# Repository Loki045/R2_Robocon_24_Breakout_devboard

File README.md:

# R2_Robocon_24_Breakout_devboard
ESP32-S3 based breakout PCB designed for Robocon 2024 R2 autonomous robot, supporting sensor interfacing, motor control, and rapid testing of navigation and ball-handling mechanisms.

# Robocon 2024 – R2 Autonomous Breakout PCB with Devboard 

This repository contains the hardware design files for the **R2 Breakout PCB** used for testing Robocon 2024 autonomous robot.

The board was designed as a **ESP32-S3 stackable breakout and testing interface**, enabling direct connection of sensors, motors, and power modules required for autonomous robot development.

---

## 📌 Robot Task Overview

In Robocon 2024, **Robot 2 (R2)** was designed as a fully autonomous robot.

Its primary tasks included:

- Following a predefined path using line follower sensors
- Navigating toward **Area 3**
- Detecting team-colored balls placed in Area 3 (Red/Blue)
- Picking balls and placing them into designated silos

The R2 with devboard breakout PCB enabled rapid testing and integration of sensors, locomotion motors, and mechanism motors required for autonomous navigation and ball placement.

---

## ⚙️ Board Overview

The R2 PCB was developed as a **Initial testing and integration platform**, allowing:

- Direct stacking of **ESP32-S3 Development Board**
- Easy connection of multiple sensors
- Support for locomotion and mechanism motors
- Clean distribution of regulated power inputs
- Rapid hardware testing during autonomous robot development

This modular design simplified debugging and allowed flexible hardware testing during algorithm development.

---

## 🔧 Key Features

- ESP32-S3 compatible stacking layout
- Multiple sensor interface connectors
- Motor control connectors
- Power input connector
- On-board LED indicators
- Decoupling capacitors for stable operation
- Pull-up / current limiting resistors
- Dedicated GPIO breakout headers

---

## 🔌 Supported Sensors

This PCB supported direct connection of commonly used autonomous sensors.

### Sensors Used:

- 6 × Luna Distance Sensors
- MPU9250 (IMU Sensor)
- LSA1 Line Follower Sensor

These sensors were used for navigation, obstacle detection, and path following.

---

## 🎮 Motor Interfaces

The board supported both locomotion and mechanism motors.

### Locomotion Motors:

- 4 Motor connectors for drive system

### Mechanism Motors:

- 2 Motor connectors for grab and lift mechanism

These motors supported locomotion and ball placement operations in silo .

---

## ⚡ Power Interface

Power was supplied through an external regulated source.

### Input:

- Power Input Connector (Voltage supplied externally)

### On-board Components:

- Capacitors for filtering
- Resistors for signal stability
- LED indicators for power/status

---

## 🧠 Application in Autonomous Robot

This breakout board enabled:

- Sensor testing and calibration
- Autonomous navigation testing
- Motor control validation
- Rapid integration of hardware modules

It played a key role in enabling the autonomous behavior of **R2 robot** during Robocon 2024.

---

## 🧰 Hardware Stack

Designed to support:

- ESP32-S3 (Main Controller)
- Line Follower Sensors
- Distance Sensors (Luna)
- MPU9250 (IMU)
- Motor Drivers
- External Power Supply

---

## 📂 Repository Contents

Images/

    ├── R2_3D.png  
    ├── R2_Bottom.png  
    ├── R2_Schematic.png  
    ├── R2_Top.png 

R2_RCU_2024-25

    ├── R2_Breakout.sch  
    ├── R2_Breakout.pcb  
    ├── R2_Breakout.pro      

.gitignore 

README.md

---

## 🛠 Tools Used

- KiCad — Schematic & PCB Design
- ESP-IDF (for ESP32-S3 firmware)

---

## 🎯 Application

This PCB was used in initial testing the **Robocon 2024 R2 Autonomous Robot**, supporting sensor integration, navigation testing, and mechanism control required for ball detection and silo placement.

---

## 👨‍💻 Contribution

Developed as part of Robocon 2024 electronics development, contributing to hardware integration and breakout design for autonomous robot testing.

---

## 📸 PCB Images

### Top Layer

### Bottom Layer

### 3D View

### Schematic

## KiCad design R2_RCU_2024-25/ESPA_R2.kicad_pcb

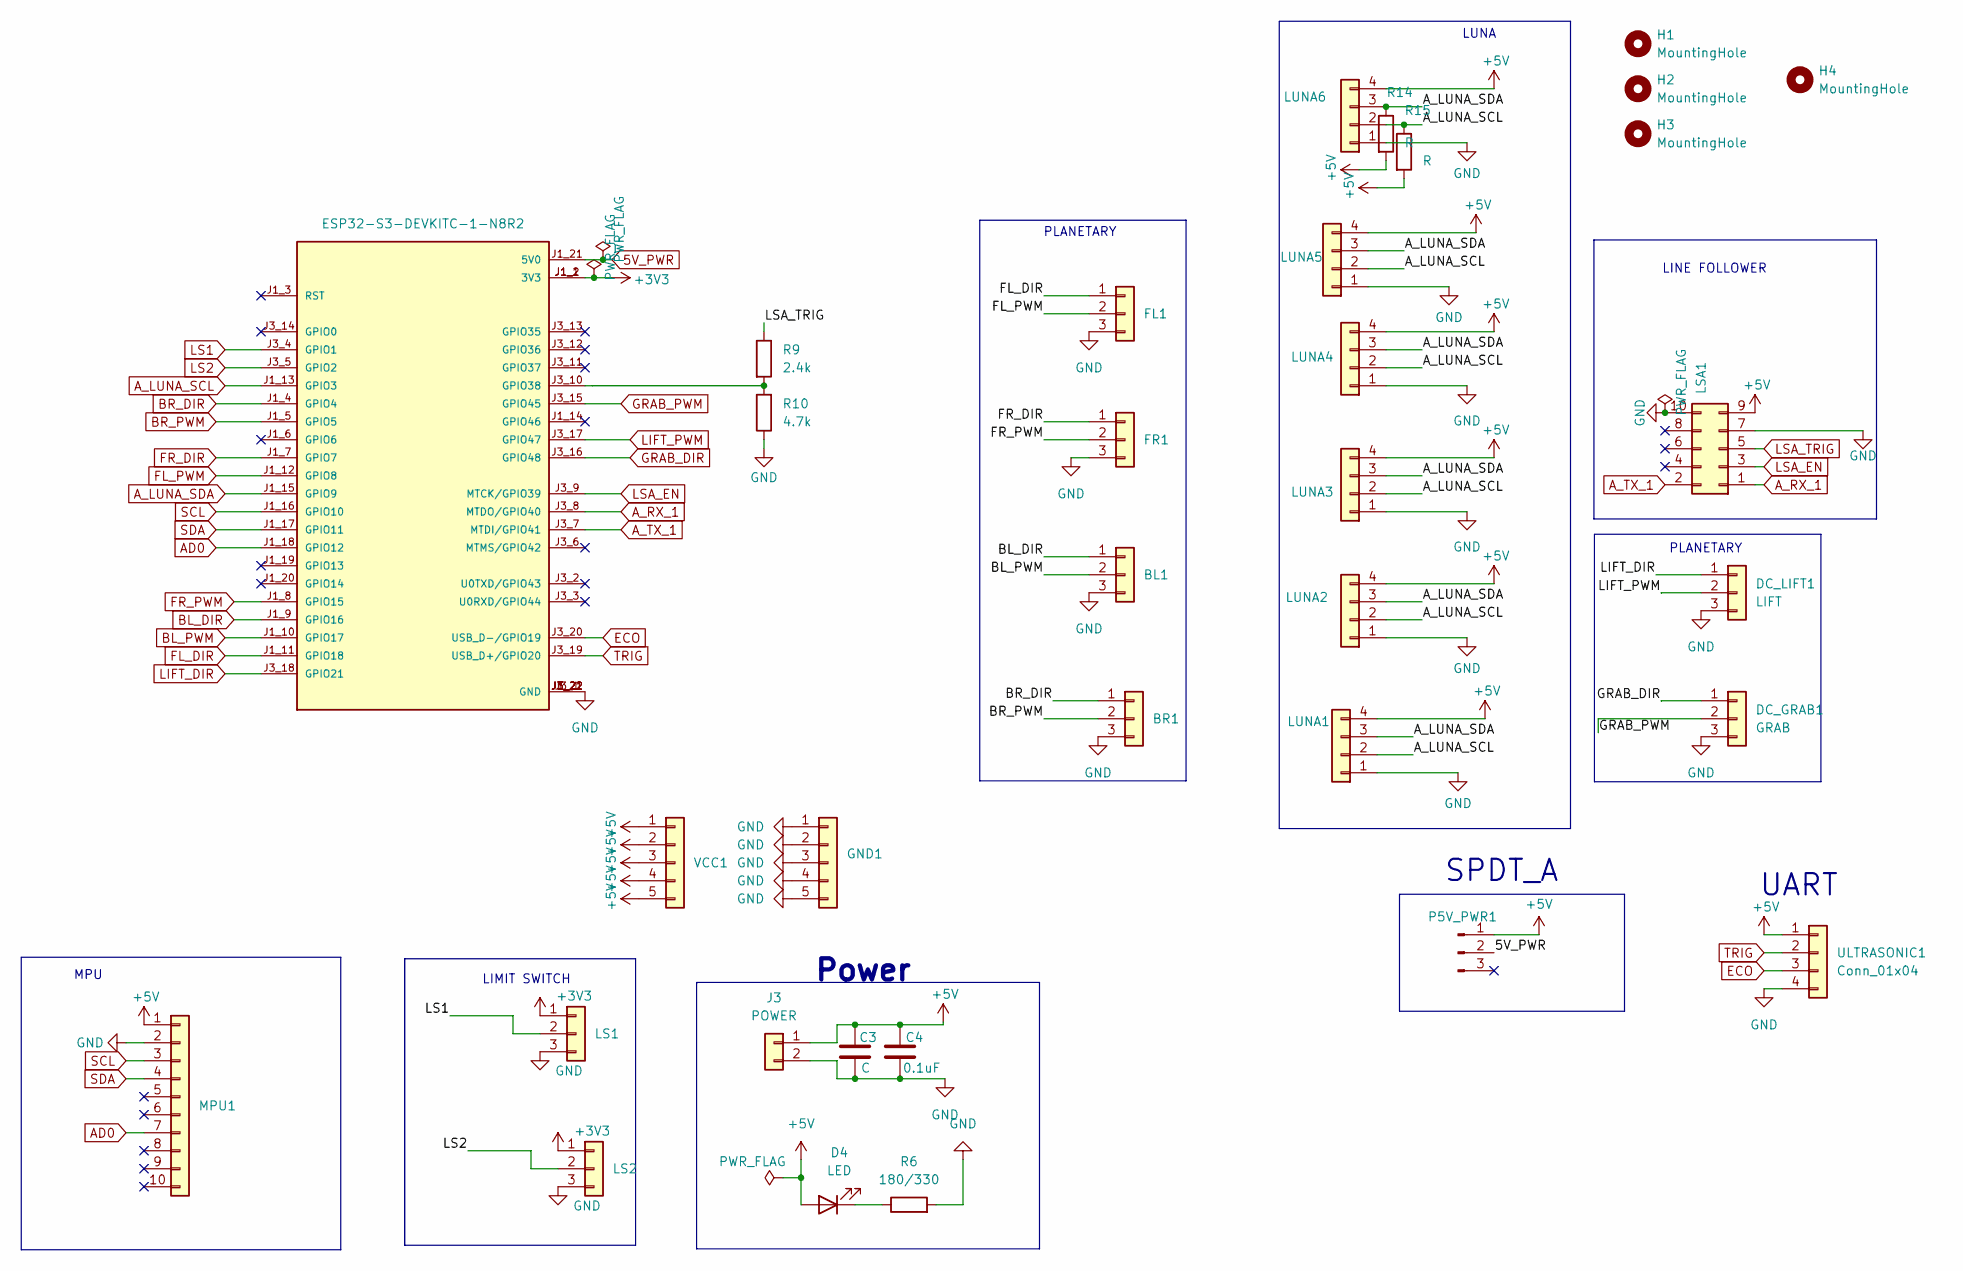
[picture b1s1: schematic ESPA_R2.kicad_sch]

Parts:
BL1: BL; JST_XH_B3B-XH-A_1x03_P2.50mm_Vertical
BR1: BR; JST_XH_B3B-XH-A_1x03_P2.50mm_Vertical
C3: C; C_Radial_D6.3mm_H11.0mm_P2.50mm
C4: 0.1uF; C_Disc_D3.0mm_W1.6mm_P2.50mm
D4: LED; LED_D5.0mm
DC_GRAB1: GRAB; JST_XH_B3B-XH-A_1x03_P2.50mm_Vertical
DC_LIFT1: LIFT; JST_XH_B3B-XH-A_1x03_P2.50mm_Vertical
ESP32-S3-DEVKITC-1-N8R2: ESP32-S3-DEVKITC-1-N8R2; XCVR_ESP32-S3-DEVKITC-1-N8R2; PARTREV V1
FL1: FL; JST_XH_B3B-XH-A_1x03_P2.50mm_Vertical
FR1: FR; JST_XH_B3B-XH-A_1x03_P2.50mm_Vertical
GND1: GND; PinHeader_1x05_P2.54mm_Vertical
H1, H2, H3, H4: MountingHole; MountingHole_2.2mm_M2_ISO14580_Pad
J3: POWER; JST_VH_B2P-VH_1x02_P3.96mm_Vertical
LS1, LS2: FR; JST_XH_B3B-XH-A_1x03_P2.50mm_Vertical
LSA1: Conn_02x05_Counter_Clockwise; IDC-Header_2x05_P2.54mm_Vertical
LUNA1: LUNA1; JST_XH_B4B-XH-A_1x04_P2.50mm_Vertical
LUNA2: LUNA2; JST_XH_B4B-XH-A_1x04_P2.50mm_Vertical
LUNA3: LUNA3; JST_XH_B4B-XH-A_1x04_P2.50mm_Vertical
LUNA4: LUNA4; JST_XH_B4B-XH-A_1x04_P2.50mm_Vertical
LUNA5: LUNA5; JST_XH_B4B-XH-A_1x04_P2.50mm_Vertical
LUNA6: LUNA6; JST_XH_B4B-XH-A_1x04_P2.50mm_Vertical
MPU1: MPU; PinSocket_1x10_P2.54mm_Vertical
P5V_PWR1: 5V_PWR; PinHeader_1x03_P2.54mm_Vertical
R6: 180/330; R_Axial_DIN0204_L3.6mm_D1.6mm_P5.08mm_Horizontal
R9: 2.4k; R_Axial_DIN0204_L3.6mm_D1.6mm_P5.08mm_Horizontal
R10: 4.7k; R_Axial_DIN0204_L3.6mm_D1.6mm_P5.08mm_Horizontal
R14, R15: R; R_Axial_DIN0204_L3.6mm_D1.6mm_P5.08mm_Horizontal
ULTRASONIC1: Conn_01x04; PinHeader_1x04_P2.54mm_Vertical
VCC1: Conn_01x05; PinHeader_1x05_P2.54mm_Vertical

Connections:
5V_PWR: ESP32-S3-DEVKITC-1-N8R2.J1_21 (5V0), P5V_PWR1.2
+3V3: ESP32-S3-DEVKITC-1-N8R2.J1_1 (3V3), ESP32-S3-DEVKITC-1-N8R2.J1_2 (3V3), LS1.1, LS2.1
+5V: C3.1, C4.2, D4.2 (A), J3.1, LSA1.9, LUNA1.4, LUNA2.4, LUNA3.4, LUNA4.4, LUNA5.4, LUNA6.4, MPU1.1, P5V_PWR1.1, R14.2, R15.2, ULTRASONIC1.1, VCC1.1, VCC1.2, VCC1.3, VCC1.4, VCC1.5
AD0: ESP32-S3-DEVKITC-1-N8R2.J1_18 (GPIO12), MPU1.7
A_LUNA_SCL: ESP32-S3-DEVKITC-1-N8R2.J1_13 (GPIO3), LUNA1.2, LUNA2.2, LUNA3.2, LUNA4.2, LUNA5.2, LUNA6.2, R15.1
A_LUNA_SDA: ESP32-S3-DEVKITC-1-N8R2.J1_15 (GPIO9), LUNA1.3, LUNA2.3, LUNA3.3, LUNA4.3, LUNA5.3, LUNA6.3, R14.1
A_RX_1: ESP32-S3-DEVKITC-1-N8R2.J3_8 (MTDO/GPIO40), LSA1.1
A_TX_1: ESP32-S3-DEVKITC-1-N8R2.J3_7 (MTDI/GPIO41), LSA1.2
BL_DIR: BL1.1, ESP32-S3-DEVKITC-1-N8R2.J1_9 (GPIO16)
BL_PWM: BL1.2, ESP32-S3-DEVKITC-1-N8R2.J1_10 (GPIO17)
BR_DIR: BR1.1, ESP32-S3-DEVKITC-1-N8R2.J1_4 (GPIO4)
BR_PWM: BR1.2, ESP32-S3-DEVKITC-1-N8R2.J1_5 (GPIO5)
ECO: ESP32-S3-DEVKITC-1-N8R2.J3_20 (USB_D-/GPIO19), ULTRASONIC1.3
FL_DIR: ESP32-S3-DEVKITC-1-N8R2.J1_11 (GPIO18), FL1.1
FL_PWM: ESP32-S3-DEVKITC-1-N8R2.J1_12 (GPIO8), FL1.2
FR_DIR: ESP32-S3-DEVKITC-1-N8R2.J1_7 (GPIO7), FR1.1
FR_PWM: ESP32-S3-DEVKITC-1-N8R2.J1_8 (GPIO15), FR1.2
GND: BL1.3, BR1.3, C3.2, C4.1, DC_GRAB1.3, DC_LIFT1.3, ESP32-S3-DEVKITC-1-N8R2.J1_22 (GND), ESP32-S3-DEVKITC-1-N8R2.J3_1 (GND), ESP32-S3-DEVKITC-1-N8R2.J3_21 (GND), ESP32-S3-DEVKITC-1-N8R2.J3_22 (GND), FL1.3, FR1.3, GND1.1, GND1.2, GND1.3, GND1.4, GND1.5, J3.2, LS1.3, LS2.3, LSA1.7, LSA1.10, LUNA1.1, LUNA2.1, LUNA3.1, LUNA4.1, LUNA5.1, LUNA6.1, MPU1.2, R6.2, R10.1, ULTRASONIC1.4
GRAB_DIR: DC_GRAB1.1, ESP32-S3-DEVKITC-1-N8R2.J3_16 (GPIO48)
GRAB_PWM: DC_GRAB1.2, ESP32-S3-DEVKITC-1-N8R2.J3_15 (GPIO45)
LIFT_DIR: DC_LIFT1.1, ESP32-S3-DEVKITC-1-N8R2.J3_18 (GPIO21)
LIFT_PWM: DC_LIFT1.2, ESP32-S3-DEVKITC-1-N8R2.J3_17 (GPIO47)
LS1: ESP32-S3-DEVKITC-1-N8R2.J3_4 (GPIO1), LS1.2
LS2: ESP32-S3-DEVKITC-1-N8R2.J3_5 (GPIO2), LS2.2
LSA_EN: ESP32-S3-DEVKITC-1-N8R2.J3_9 (MTCK/GPIO39), LSA1.3
LSA_TRIG: LSA1.5, R9.1
unnamed: D4.1 (K), R6.1
unnamed: ESP32-S3-DEVKITC-1-N8R2.J3_10 (GPIO38), R9.2, R10.2
SCL: ESP32-S3-DEVKITC-1-N8R2.J1_16 (GPIO10), MPU1.3
SDA: ESP32-S3-DEVKITC-1-N8R2.J1_17 (GPIO11), MPU1.4
TRIG: ESP32-S3-DEVKITC-1-N8R2.J3_19 (USB_D+/GPIO20), ULTRASONIC1.2

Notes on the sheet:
UART
LIMIT SWITCH
MPU
PLANETARY
SPDT_A
LUNA
LINE FOLLOWER
Power
PLANETARY

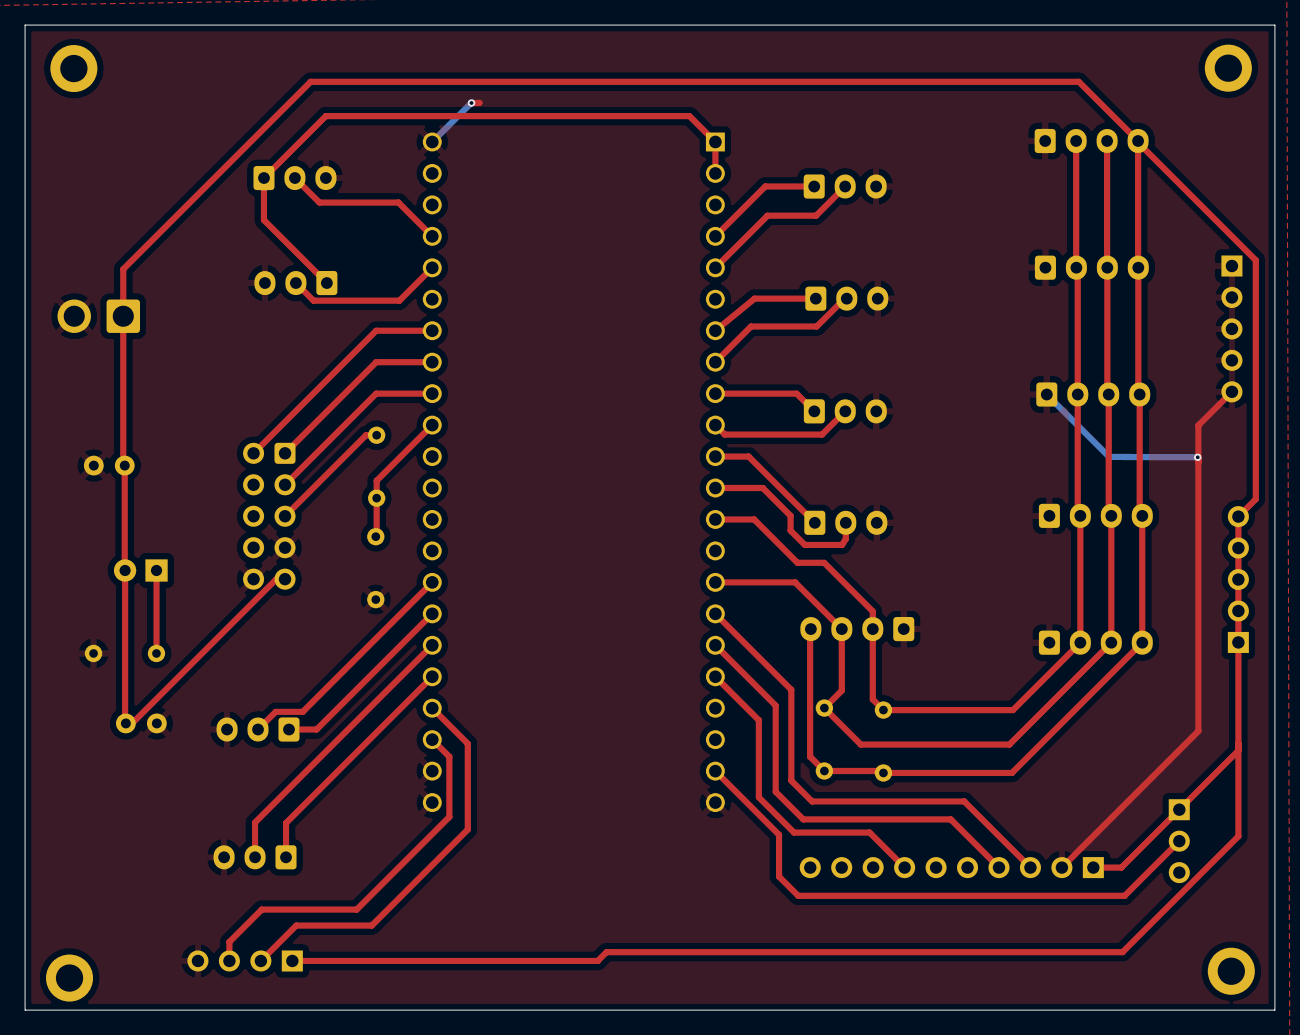
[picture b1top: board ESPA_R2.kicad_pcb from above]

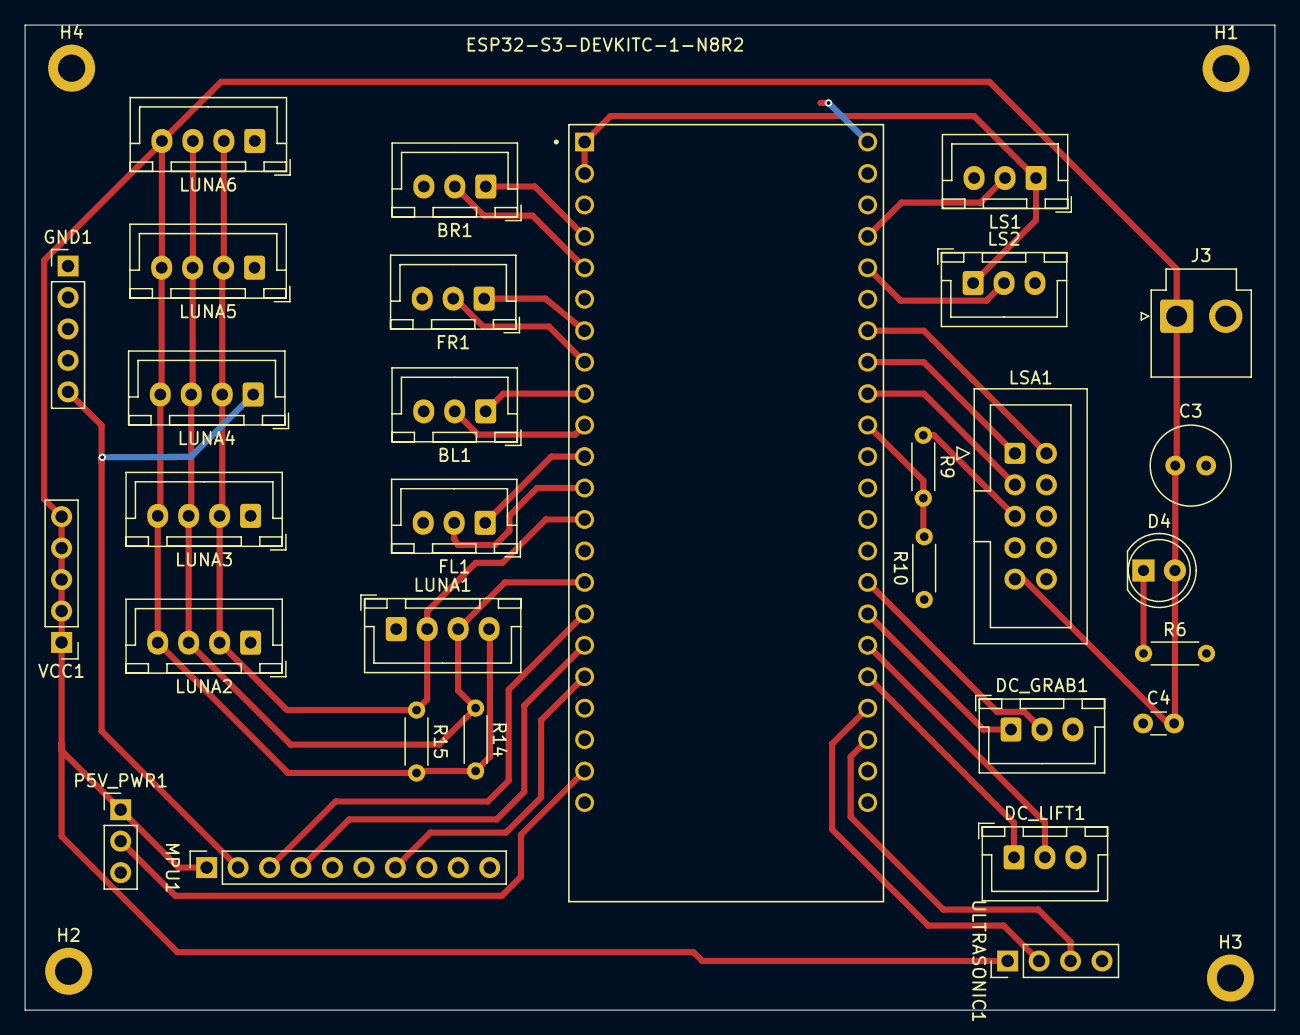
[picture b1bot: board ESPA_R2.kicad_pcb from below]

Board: 2 copper layers, 100.9 x 79.5 mm, 34 parts (34 on the bottom side), 31 nets.

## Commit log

2026-04-18 Images added
